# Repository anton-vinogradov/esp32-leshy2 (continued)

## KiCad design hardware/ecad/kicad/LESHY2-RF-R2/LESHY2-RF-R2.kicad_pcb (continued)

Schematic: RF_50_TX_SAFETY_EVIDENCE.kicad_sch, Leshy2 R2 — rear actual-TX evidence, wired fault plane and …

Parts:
C262, C287, C288: TDK C1608X7R1C105K080AC; C_0603_1608Metric
C263, C264, C265, C266, C267, C268, C269, C270, C271, C272, C273, C274, C276, C277, C278, C280, C282, C283, C284, C285, C286: Yageo CC0402KRX7R9BB104; C_0402_1005Metric
C275: Murata GRM21BR71E225KE11L; C_0805_2012Metric
C279: Murata GRM188R60J106ME47D; C_0603_1608Metric
C281: Murata GRM155R71H103KA88D; C_0402_1005Metric
J13: Samtec FTSH-105-01-L-DV-K-P-TR; FTSH-105-01-L-DV-K-P-TR
Q6: NX3008NBKS,115; SOT-363_SC-70-6
R249, R250, R252, R253, R255, R256, R257, R258, R259, R260, R261, R263, R266, R267, R268, R269, R271, R273, R274, R275, R276, R277, R278, R279, R280, R282, R283, R285, R287: Yageo RC0402FR-0710KL; R_0402_1005Metric
R251, R262, R281, R286: Yageo RC0402FR-071ML; R_0402_1005Metric
R254, R264, R270, R284, R288: Yageo RC0402FR-07100KL; R_0402_1005Metric
R265, R272: Yageo RC0402FR-0747KL; R_0402_1005Metric
SW5: C&K JS102011SAQN; SW_SPDT_CK_JS102011SAQN
U107, U133, U134: Diodes Incorporated BAT54-7-F; SOT-23
U108, U109, U110: TLV1821DCKR; Texas_R-PDSO-G5_DCK-5
U111: TCA9535PWR; TSSOP-24_4.4x7.8mm_P0.65mm
U112, U113, U114, U115, U116: BAT54ALT1G; SOT-23
U117: 74LVC2G14GV,125; SC-74-6_1.55x2.9mm_P0.95mm
U118: SN74LVC3G07DCUR; VSSOP-8_2.3x2mm_P0.5mm
U119: SN74LVC08APWR; TSSOP-14_4.4x5mm_P0.65mm
U120: SN74LVC1G74DCUR; VSSOP-8_2.3x2mm_P0.5mm
U121: 74LVC1G32GV,125; SC-74A-5_1.55x2.9mm_P0.95mm
U122: SN74LVC1G17DCKR; SOT-353_SC-70-5
U123: Texas Instruments SN74LVC1G06DCKR; Texas_R-PDSO-G5_DCK-5
U124, U128, U129, U131, U132: SN74LVC1G07DCKR; Texas_R-PDSO-G5_DCK-5
U125: TPS3808G33DBVR; SOT-23-6
U126: Texas Instruments TPD4E05U06DQAR; USON-10_2.5x1.0mm_P0.5mm
U127: Texas Instruments MSPM0C1106SDGS20R; Texas_DGS0020A_TSSOP-20_3x5.1mm_P0.5mm
U130: Texas Instruments TPS3435CAKAGDDFR; Texas_DDF0008A_SOT-8_1.6x2.9mm_P0.65mm

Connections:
/RF_01_USB_PD_CHARGE/AON_SAFE_3V3: C263.1 (END_1), C264.1 (END_1), C265.1 (END_1), C266.1 (END_1), C269.1 (END_1), C270.1 (END_1), C271.1 (END_1), C272.1 (END_1), C273.1 (END_1), C274.1 (END_1), C276.1 (END_1), C277.1 (END_1), C278.1 (END_1), C279.1 (END_1), C280.1 (END_1), C282.1 (END_1), C283.1 (END_1), C284.1 (END_1), C285.1 (END_1), C286.1 (END_1), J13.2, R249.1 (END_1), R252.1 (END_1), R254.1 (END_1), R259.1 (END_1), R260.1 (END_1), R261.1 (END_1), R263.1 (END_1), R267.1 (END_1), R268.1 (END_1), R269.1 (END_1), R272.1 (END_1), R275.1 (END_1), R277.1 (END_1), R282.1 (END_1), R284.1 (END_1), R288.1 (END_1), U108.5 (VPLUS), U109.5 (VPLUS), U110.5 (VPLUS), U111.24 (VCC), U117.5 (VCC), U118.8 (VCC), U119.14 (VCC), U120.7 (PRE_N), U120.8 (VCC), U121.5 (VCC), U122.5 (VCC), U123.5 (VCC), U124.5 (VCC), U125.5 (SENSE), U125.6 (VDD), U127.6 (VDD), U128.5 (VCC), U129.5 (VCC), U130.6 (WD_EN), U130.8 (VDD), U131.5 (VCC), U132.5 (VCC); also elsewhere on the board
/RF_01_USB_PD_CHARGE/POWER_GROUND: C262.2 (END_2), C263.2 (END_2), C264.2 (END_2), C265.2 (END_2), C266.2 (END_2), C267.2 (END_2), C268.2 (END_2), C269.2 (END_2), C270.2 (END_2), C271.2 (END_2), C272.2 (END_2), C273.2 (END_2), C274.2 (END_2), C275.2 (END_2), C276.2 (END_2), C277.2 (END_2), C278.2 (END_2), C279.2 (END_2), C280.2 (END_2), C281.2 (END_2), C282.2 (END_2), C283.2 (END_2), C284.2 (END_2), C285.2 (END_2), C286.2 (END_2), C287.2 (END_2), C288.2 (END_2), J13.1, J13.7, J13.9, Q6.1 (S1), Q6.2 (G1), Q6.4 (S2), R250.2 (END_2), R253.2 (END_2), R255.2 (END_2), R256.2 (END_2), R257.2 (END_2), R258.2 (END_2), R262.2 (END_2), R273.2 (END_2), R274.2 (END_2), R276.2 (END_2), R280.2 (END_2), R283.2 (END_2), R285.2 (END_2), R287.2 (END_2), SW5.2 (COMMON), U108.2 (VMINUS), U109.2 (VMINUS), U110.2 (VMINUS), U111.2 (A1), U111.3 (A2), U111.12 (GND), U111.21 (A0), U117.2 (GND), U118.4 (GND), U119.7 (GND), U120.4 (GND), U121.3 (GND), U122.3 (GND), U123.3 (GND), U124.3 (GND), U125.2 (GND), U126.3 (GND_3), U126.8 (GND_8), U127.7 (VSS), U128.3 (GND), U129.3 (GND), U130.1 (SET0), U130.4 (GND), U130.5 (SET1), U131.3 (GND), U132.3 (GND); also elsewhere on the board
/RF_02_PACK_SAFETY_AON/3V3_MAIN: R266.1 (END_1), R271.1 (END_1), R278.1 (END_1), R279.1 (END_1); also elsewhere on the board
/RF_02_PACK_SAFETY_AON/HUB_SAFE_I2C_SCL_AON: U127.11 (PA11); also elsewhere on the board
/RF_02_PACK_SAFETY_AON/HUB_SAFE_I2C_SDA_AON: U127.4 (PA0); also elsewhere on the board
/RF_02_PACK_SAFETY_AON/PACK_ADMISSION_VDD: R265.1 (END_1); also elsewhere on the board
/RF_03_MAIN_RAILS_DOMAIN_GATES/AON_PG_N: U125.3 (MR_N); also elsewhere on the board
/RF_03_MAIN_RAILS_DOMAIN_GATES/EV_N8_LORA_EXT: U111.13 (P10), U116.1 (K1); also elsewhere on the board
/RF_03_MAIN_RAILS_DOMAIN_GATES/EXT_ANY_5V_EN_SAFE: U119.11 (4Y); also elsewhere on the board
/RF_03_MAIN_RAILS_DOMAIN_GATES/EXT_ANY_5V_REQ: U119.12 (4A); also elsewhere on the board
/RF_03_MAIN_RAILS_DOMAIN_GATES/FAULT_ASSERT_N: R262.1 (END_1), R263.2 (END_2), R264.1 (END_1), R277.2 (END_2), U118.1 (1A), U118.2 (3Y), U118.3 (2A), U119.10 (3B), U124.4 (Y), U128.4 (Y), U130.7 (WDO_N); also elsewhere on the board
/RF_03_MAIN_RAILS_DOMAIN_GATES/POR_N: R269.2 (END_2), U119.9 (3A), U125.1 (RESET_N); also elsewhere on the board
/RF_03_MAIN_RAILS_DOMAIN_GATES/POWER_FAULT_N: R266.2 (END_2), U127.3 (PA30); also elsewhere on the board
/RF_03_MAIN_RAILS_DOMAIN_GATES/POWER_ZONE_TEMP_ADC: U127.1 (PA26); also elsewhere on the board
/RF_03_MAIN_RAILS_DOMAIN_GATES/RF_ZONE_TEMP_ADC: U127.2 (PA27); also elsewhere on the board
/RF_10_RP2354_CORE_SERVICE/CC_PWR_EN: U119.1 (1A); also elsewhere on the board
/RF_10_RP2354_CORE_SERVICE/RF_ANY_TX_N: U132.4 (Y); also elsewhere on the board
/RF_10_RP2354_CORE_SERVICE/RF_RP_RESET_N: Q6.3 (D2), U118.7 (1Y); also elsewhere on the board
/RF_10_RP2354_CORE_SERVICE/RF_SLOW_IO_ALERT: U117.4 (2Y); also elsewhere on the board
/RF_10_RP2354_CORE_SERVICE/VOICE_PTT_REQ_N: U121.2 (1A); also elsewhere on the board
/RF_20_CC1101_VOICE_TX/CC_DETECT_V: U108.4 (IN_N); also elsewhere on the board
/RF_20_CC1101_VOICE_TX/CC_PWR_EN_PRIMARY: U119.3 (1Y); also elsewhere on the board
/RF_20_CC1101_VOICE_TX/CC_PWR_EN_SAFE: U107.1 (A); also elsewhere on the board
/RF_20_CC1101_VOICE_TX/VOICE_DETECT_V: U109.4 (IN_N); also elsewhere on the board
/RF_20_CC1101_VOICE_TX/VOICE_DOMAIN_EN_SAFE: U119.6 (2Y), U133.1 (A), U134.1 (A); also elsewhere on the board
/RF_20_CC1101_VOICE_TX/VOICE_EFUSE_BACKUP_EN_N: U118.5 (2Y); also elsewhere on the board
/RF_20_CC1101_VOICE_TX/VOICE_PTT_SAFE_N: U121.4 (1Y); also elsewhere on the board
/RF_20_CC1101_VOICE_TX/VOICE_V_DETECT_V: U110.4 (IN_N); also elsewhere on the board
/RF_30_U214_U219_M5_EXT/EV_N9_U219_NFC: U111.20 (P17), U116.2 (K2); also elsewhere on the board
/RF_31_REAR_CONTROLS/VOICE_DOMAIN_REQ: U119.4 (2A); also elsewhere on the board
/RF_40_INTERBOARD_M1/S3_RESET_KILL_GATE: U129.4 (Y); also elsewhere on the board
/RF_40_INTERBOARD_M1/UI_ZONE_TEMP_ADC: U127.12 (PA16); also elsewhere on the board
/RF_50_TX_SAFETY_EVIDENCE/ANY_TX_AON_N: R249.2 (END_2), U112.3 (A_COMMON), U113.3 (A_COMMON), U114.3 (A_COMMON), U115.3 (A_COMMON), U116.3 (A_COMMON), U127.17 (PA22), U132.2 (A)
/RF_50_TX_SAFETY_EVIDENCE/AON_SERVICE_RELEASE_REQ: R257.1 (END_1), U111.17 (P14); also elsewhere on the board
/RF_50_TX_SAFETY_EVIDENCE/C5_MUX_SEL_REQUEST: R255.1 (END_1), U111.15 (P12); also elsewhere on the board
/RF_50_TX_SAFETY_EVIDENCE/C5_SERVICE_OWNED: R258.1 (END_1), U111.18 (P15); also elsewhere on the board
/RF_50_TX_SAFETY_EVIDENCE/C5_SERVICE_PATH_ACK: R256.1 (END_1), U111.16 (P13); also elsewhere on the board
/RF_50_TX_SAFETY_EVIDENCE/CC_EVIDENCE_HOLD: C262.1 (END_1), R250.1 (END_1), U107.3 (K); also elsewhere on the board
/RF_50_TX_SAFETY_EVIDENCE/EV_N0_S3: U111.4 (P00), U112.1 (K1); also elsewhere on the board
/RF_50_TX_SAFETY_EVIDENCE/EV_N1_C5: U111.5 (P01), U112.2 (K2); also elsewhere on the board
/RF_50_TX_SAFETY_EVIDENCE/EV_N2_NRF0: U111.6 (P02), U113.1 (K1); also elsewhere on the board
/RF_50_TX_SAFETY_EVIDENCE/EV_N3_NRF1: U111.7 (P03), U113.2 (K2); also elsewhere on the board
/RF_50_TX_SAFETY_EVIDENCE/EV_N4_NRF2: U111.8 (P04), U114.1 (K1); also elsewhere on the board
/RF_50_TX_SAFETY_EVIDENCE/EV_N5_CC: R251.1 (END_1), R252.2 (END_2), U108.1 (OUT), U111.9 (P05), U114.2 (K2); also elsewhere on the board
/RF_50_TX_SAFETY_EVIDENCE/EV_N6_VOICE: R281.1 (END_1), R282.2 (END_2), R286.1 (END_1), U109.1 (OUT), U110.1 (OUT), U111.10 (P06), U115.1 (K1); also elsewhere on the board
/RF_50_TX_SAFETY_EVIDENCE/EV_N7_IR: U111.11 (P07), U115.2 (K2); also elsewhere on the board
/RF_50_TX_SAFETY_EVIDENCE/EV_THRESH_5_CC: R251.2 (END_2), R253.1 (END_1), R254.2 (END_2), U108.3 (IN_P)
/RF_50_TX_SAFETY_EVIDENCE/EV_THRESH_6_VOICE: R281.2 (END_2), R283.1 (END_1), R284.2 (END_2), U109.3 (IN_P)
/RF_50_TX_SAFETY_EVIDENCE/EV_THRESH_6_VOICE_V: R286.2 (END_2), R287.1 (END_1), R288.2 (END_2), U110.3 (IN_P)
/RF_50_TX_SAFETY_EVIDENCE/FAULT_ASSERT_SENSE: R264.2 (END_2), U111.14 (P11)
/RF_50_TX_SAFETY_EVIDENCE/FAULT_KILL: U120.3 (Q_N), U121.1 (1B), U131.2 (A); also elsewhere on the board
/RF_50_TX_SAFETY_EVIDENCE/FAULT_LATCH_SENSE: R278.2 (END_2), U131.4 (Y); also elsewhere on the board
/RF_50_TX_SAFETY_EVIDENCE/HUB_AON_ALERT_N: R259.2 (END_2), U111.19 (P16); also elsewhere on the board
/RF_50_TX_SAFETY_EVIDENCE/POWER_COMMAND_OFF_N: C267.1 (END_1), R265.2 (END_2), SW5.3 (THROW_B), U118.6 (3A); also elsewhere on the board
/RF_50_TX_SAFETY_EVIDENCE/RF_RESET_KILL_GATE: Q6.5 (G2), R271.2 (END_2), U123.4 (Y)
/RF_50_TX_SAFETY_EVIDENCE/RF_SLOW_IO_INT_N: R279.2 (END_2), U117.3 (2A); also elsewhere on the board
/RF_50_TX_SAFETY_EVIDENCE/RUN_EDGE: R270.1 (END_1), U117.6 (1Y), U124.2 (A), U127.19 (PA24)
/RF_50_TX_SAFETY_EVIDENCE/RUN_LOOP_RAW: C268.1 (END_1), R267.2 (END_2), SW5.1 (THROW_A), U117.1 (1A), U126.1 (D1_PLUS)
/RF_50_TX_SAFETY_EVIDENCE/RUN_PERMIT: U119.2 (1B), U119.5 (2B), U119.13 (4B), U120.5 (Q), U123.2 (A); also elsewhere on the board
/RF_50_TX_SAFETY_EVIDENCE/S3_FAULT_RESET_REQUEST: R274.1 (END_1), U127.18 (PA23), U129.2 (A)
/RF_50_TX_SAFETY_EVIDENCE/SAFETY_CONTROLLER_NRST_N: C281.1 (END_1), J13.3, R272.2 (END_2), U127.5 (PA1_NRST)
/RF_50_TX_SAFETY_EVIDENCE/SAFETY_EVIDENCE_I2C_SCL: R260.2 (END_2), U111.22 (SCL), U127.8 (PA2)
/RF_50_TX_SAFETY_EVIDENCE/SAFETY_EVIDENCE_I2C_SDA: R261.2 (END_2), U111.23 (SDA), U127.9 (PA4)
/RF_50_TX_SAFETY_EVIDENCE/SAFETY_FAULT_REQUEST: R273.1 (END_1), U127.20 (PA25), U128.2 (A)
/RF_50_TX_SAFETY_EVIDENCE/SAFETY_SERVICE_UART_RX: J13.5, U127.14 (PA18)
/RF_50_TX_SAFETY_EVIDENCE/SAFETY_SERVICE_UART_TX: J13.4, U127.13 (PA17)
/RF_50_TX_SAFETY_EVIDENCE/SAFETY_SWCLK: J13.8, U127.16 (PA20_SWCLK)
/RF_50_TX_SAFETY_EVIDENCE/SAFETY_SWDIO: J13.6, U127.15 (PA19_SWDIO)
/RF_50_TX_SAFETY_EVIDENCE/SAFETY_WATCHDOG_MR_N: R275.2 (END_2), U130.2 (MR_N)
/RF_50_TX_SAFETY_EVIDENCE/SAFETY_WATCHDOG_WDI: R276.1 (END_1), U127.10 (PA6), U130.3 (WDI)
/RF_50_TX_SAFETY_EVIDENCE/SAFE_CLEAR_N: U119.8 (3Y), U120.6 (CLR_N)
/RF_50_TX_SAFETY_EVIDENCE/SAFE_D_HIGH: R268.2 (END_2), U120.2 (D)
/RF_50_TX_SAFETY_EVIDENCE/SAFE_REARM_CLK: U120.1 (CLK), U122.4 (Y)
/RF_50_TX_SAFETY_EVIDENCE/SAFE_REARM_DELAY: C275.1 (END_1), R270.2 (END_2), U122.2 (A)
/RF_50_TX_SAFETY_EVIDENCE/VOICE_EVIDENCE_HOLD: C287.1 (END_1), R280.1 (END_1), U133.3 (K); also elsewhere on the board
/RF_50_TX_SAFETY_EVIDENCE/VOICE_V_EVIDENCE_HOLD: C288.1 (END_1), R285.1 (END_1), U134.3 (K); also elsewhere on the board

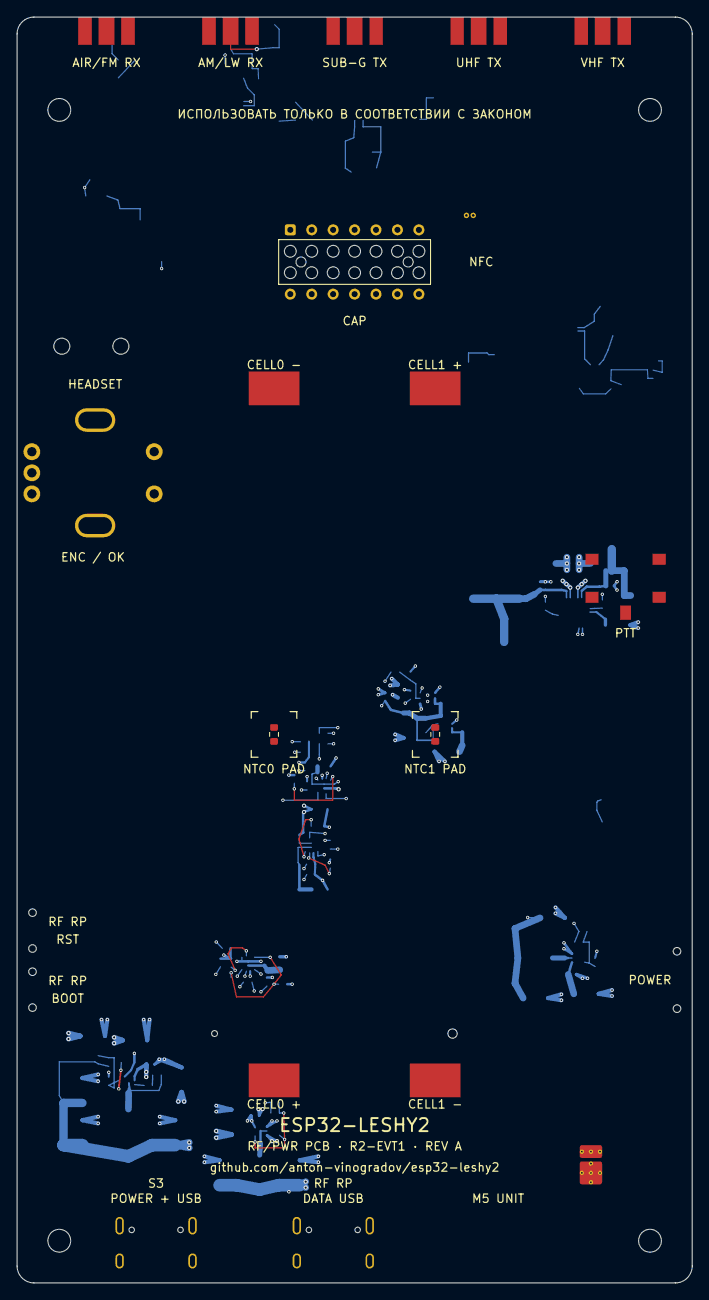
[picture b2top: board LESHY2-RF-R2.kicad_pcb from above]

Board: 6 copper layers, 80.0 x 150.0 mm, 784 parts (768 on the bottom side), 516 nets.

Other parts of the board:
MH1, MH2, MH3, MH4: M2.5 compression-stop axis; MountingHole_2.7mm_M2.5

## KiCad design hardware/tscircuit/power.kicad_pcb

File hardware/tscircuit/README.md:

# Current ECAD status

There is **no current Leshy2 schematic or PCB layout in this directory yet**.
The previous tscircuit sheets and their partial KiCad exports were moved to
[`drafts/legacy-2026-08-22/tscircuit-pre-g2f3i`](../../drafts/legacy-2026-08-22/tscircuit-pre-g2f3i/)
because they describe a superseded device: 80-mm boards, a 4-inch ST7796
display, discrete D-pad buttons, STOP, onboard LoRa, SA868 and the old
controller/resource assignment.

Those files are retained only as historical implementation material. They must
not be built, reviewed as the current circuit or sent to a PCB manufacturer.

The current electrical source is the machine-reviewed `G2F-3I` architecture in
[`hardware/architecture`](../architecture/). H1 has been accepted and H2 now
authorizes a new reviewable production schematic generated from that source.
KiCad PCB placement and routing remain unauthorized until the current
schematic, ERC, power/fault simulation and joined mechanical/electrical/firmware
review pass.

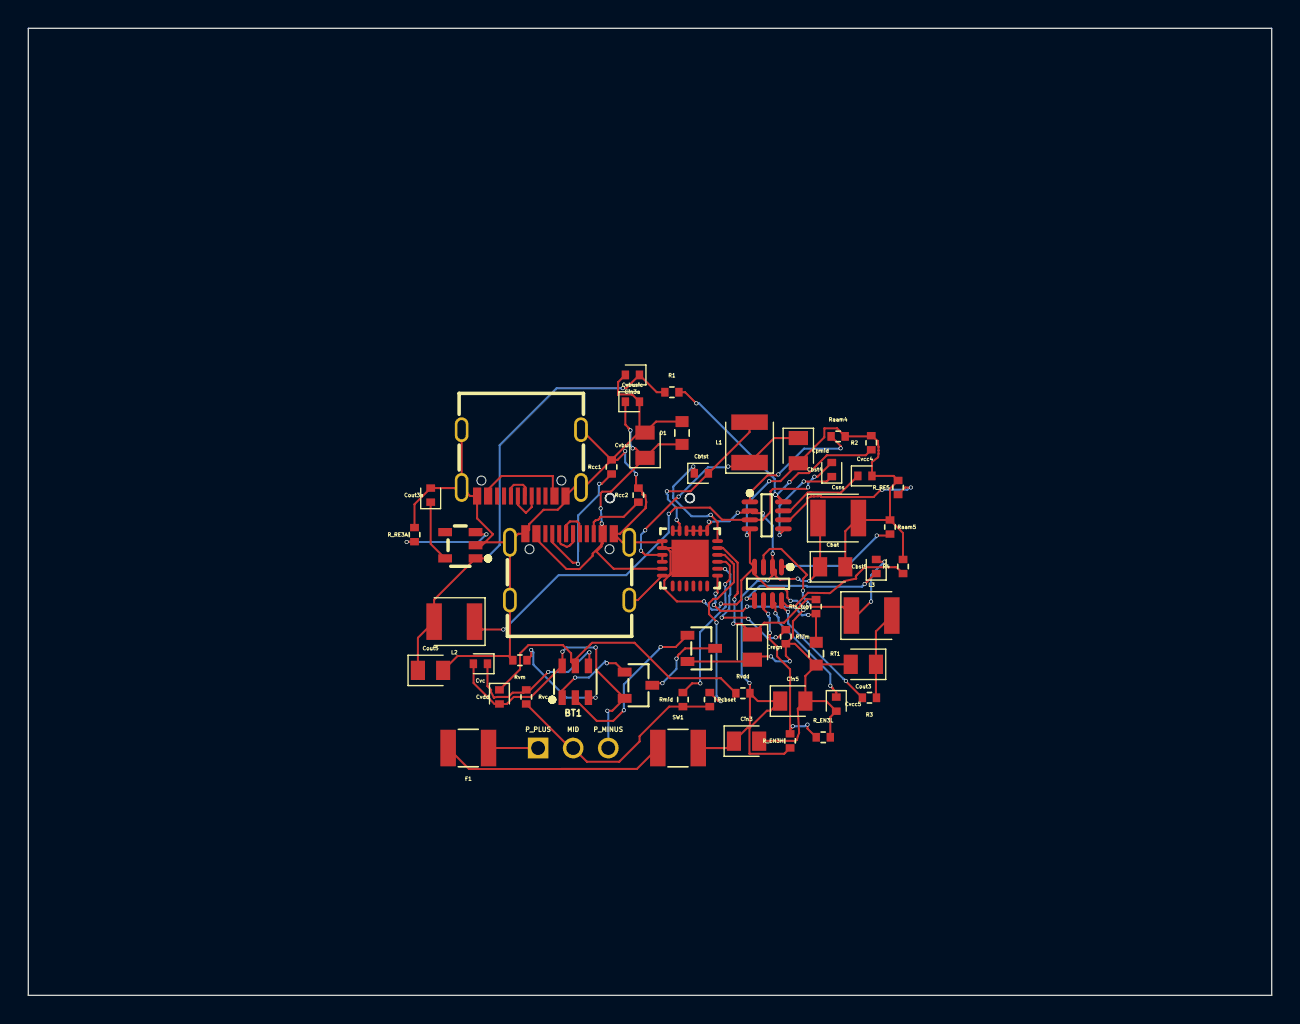
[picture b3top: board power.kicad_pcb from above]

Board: 2 copper layers, 90.0 x 70.0 mm, 55 parts (0 on the bottom side), 44 nets.

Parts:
BT1: chip_pinrow3
Cbat: 10uF; capacitor_cap0805
Cbst4, Cbst5: 100nF; capacitor_cap0402
Cbtst: 47nF; capacitor_cap0402
Cin3, Cin5: 22uF; capacitor_cap0805
Cin3a: 1uF; capacitor_cap0402
Cout3, Cout5: 22uF; capacitor_cap0805
Cout3a: 2.2uF; capacitor_cap0402
Cpmid: 10uF; capacitor_cap0805
Cregn: 4.7uF; capacitor_cap0805
Csns: 47uF; capacitor_cap1210
Cvbus: 10uF; capacitor_cap0805
Cvbusic: 1uF; capacitor_cap0402
Cvc: 0.1uF; capacitor_cap0402
Cvcc4, Cvcc5: 0.1uF; capacitor_cap0402
Cvdd: 0.1uF; capacitor_cap0402
D1: 1MΩ; resistor_res0603
F1: 50mΩ; resistor_res1210
J1, J2: chip
L1, L3: 2.2µH; inductor_1210
L2: 4.7µH; inductor_1210
Q1, Q2: chip
R1: 52.3kΩ; resistor_res0402
R2, R4: 10kΩ; resistor_res0402
R3: 31.6kΩ; resistor_res0402
RT1: 10kΩ; resistor_res0603
R_EN3H: 100kΩ; resistor_res0402
R_EN3L: 47kΩ; resistor_res0402
R_RE3A, R_RE5: 100kΩ; resistor_res0402
Raam4, Raam5: 100kΩ; resistor_res0402
Rcbset: 10Ω; resistor_res0402
Rcc1, Rcc2: 5.1kΩ; resistor_res0402
Rilim: 383Ω; resistor_res0402
Rmid: 300Ω; resistor_res0402
Rts_top: 5.23kΩ; resistor_res0402
Rvc: 470Ω; resistor_res0402
Rvdd: 470Ω; resistor_res0402
Rvm: 2kΩ; resistor_res0402
SW1: 10mΩ; resistor_res1210
U2, U3, U4, U5, U6: chip

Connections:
.BT1 > .P_PLUS to .F1 > .pin1: BT1.1, F1.1
.Cbst4 > .pin1 to .U4 > .BST: Cbst4.1, U4.5
.Cbst5 > .pin1 to .U5 > .BST: Cbst5.1, U5.5
.Cbtst > .pin1 to .U2 > .BTST: Cbtst.1, U2.12
.Cregn > .pin1 to .U2 > .REGN: Cregn.1, Rts_top.1, U2.11
.Cvcc4 > .pin1 to .U4 > .VCC: Cvcc4.1, U4.7
.Cvcc5 > .pin1 to .U5 > .VCC: Cvcc5.1, U5.7
.F1 > .pin2 to .SW1 > .pin1: F1.2, SW1.1
.R1 > .pin2 to .U4 > .FB: R1.2, R2.1, U4.8
.R3 > .pin2 to .U5 > .FB: R3.2, R4.1, U5.8
.R_EN3H > .pin2 to .U5 > .pin6: R_EN3H.2, R_EN3L.1, U5.6
.Raam4 > .pin1 to .U4 > .AAM: Raam4.1, U4.1
.Raam5 > .pin1 to .U5 > .AAM: Raam5.1, U5.1
.Rcbset > .pin1 to .U2 > .CBSET: Rcbset.1, U2.10
.Rcc1 > .pin1 to .J1 > .CC1: J1.13, Rcc1.1
.Rcc2 > .pin1 to .J1 > .CC2: J1.7, Rcc2.1
.Rilim > .pin1 to .U2 > .ILIM: Rilim.1, U2.8
.Rmid > .pin1 to .U2 > .MID: Rmid.1, U2.9
.Rvc > .pin1 to .U3 > .VC: Cvc.1, Rvc.1, U3.4
.Rvdd > .pin1 to .U3 > .VDD: Cvdd.1, Rvdd.1, U3.5
.Rvm > .pin1 to .U3 > .VM: Rvm.1, U3.3
.U3 > .CO to .Q2 > .G: Q2.1, U3.2
.U3 > .DO to .Q1 > .G: Q1.1, U3.1
.U4 > .SW to .L2 > .pin1: Cbst4.2, L2.1, U4.3
.U5 > .SW to .L3 > .pin1: Cbst5.2, L3.1, U5.3
BAT: Cbat.1, Cin3.1, Cin5.1, Csns.1, R_EN3H.1, Rvdd.2, SW1.2, U2.13, U2.14, U2.15, U2.16, U4.2, U5.2
BATM: BT1.2, Rcbset.2, Rmid.2, Rvc.2
BMINUS: BT1.3, Cvc.2, Cvdd.2, Q1.2, U3.6
GND: Cbat.2, Cin3.2, Cin3a.2, Cin5.2, Cout3.2, Cout3a.2, Cout5.2, Cpmid.2, Cregn.2, Csns.2, Cvbus.2, Cvbusic.2, Cvcc4.2, Cvcc5.2, D1.2, J1.1, J1.2, J1.3, J1.4, J1.5, J1.16, J2.1, J2.2, J2.3, J2.4, J2.5, J2.16, Q2.2, R2.2, R4.2, RT1.2, R_EN3L.2, R_RE3A.2, R_RE5.2, Raam4.2, Raam5.2, Rcc1.2, Rcc2.2, Rilim.2, Rvm.2, U2.19, U2.20, U2.24, U2.25, U4.4, U5.4, U6.2
PACKMID: Q1.3, Q2.3
PMID: Cpmid.1, L1.1, U2.21, U2.22
RAIL_EN_3V3A: R_RE3A.1, U6.3
RAIL_EN_5V: R_RE5.1, U4.6
SW: Cbtst.2, L1.2, U2.17, U2.18
TS: RT1.1, Rts_top.2, U2.7
USB_DM_C5: J2.10, J2.12
USB_DM_S3: J1.10, J1.12
USB_DP_C5: J2.9, J2.11
USB_DP_S3: J1.9, J1.11
V3V3: Cout3.1, L3.2, R3.1
V3V3A: Cout3a.1, U6.5
V5: Cin3a.1, Cout5.1, L2.2, R1.1, U6.1
VBUS_C5: J2.6, J2.15
VBUS_S3: Cvbus.1, Cvbusic.1, D1.1, J1.6, J1.15, U2.23

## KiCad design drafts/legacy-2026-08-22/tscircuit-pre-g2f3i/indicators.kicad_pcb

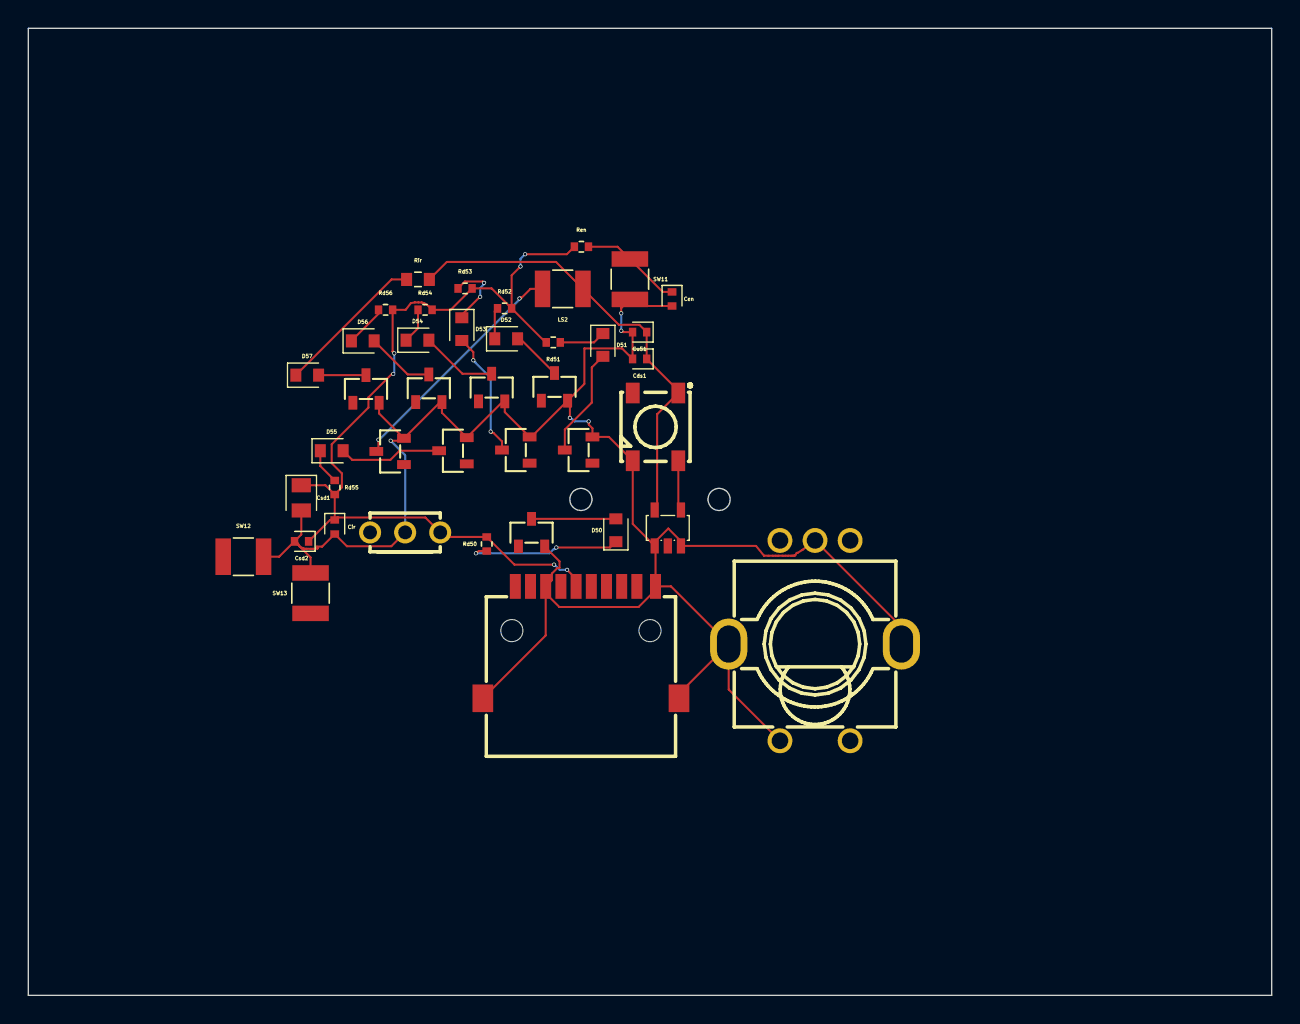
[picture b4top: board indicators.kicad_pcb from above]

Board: 2 copper layers, 90.0 x 70.0 mm, 41 parts (0 on the bottom side), 22 nets.

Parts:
Cds1: 100nF; capacitor_cap0402
Cen: 1uF; capacitor_cap0402
Cir: 100nF; capacitor_cap0402
Csd1: 10uF; capacitor_cap0805
Csd2: 100nF; capacitor_cap0402
Cu51: 100nF; capacitor_cap0402
D50, D51, D52, D53, D54, D55, D56, D57: LED; led_0603
DS1: chip
J50: chip
LS2: 10mΩ; resistor_res1210
Q50, Q51, Q52, Q53, Q54, Q55, Q56, Q57, Q58: chip
Rd50, Rd51, Rd52, Rd53, Rd54, Rd55, Rd56: 4.7kΩ; resistor_res0402
Ren: 10kΩ; resistor_res0402
Rir: 47Ω; resistor_res0603
SW10: chip
SW11, SW12, SW13: 10mΩ; resistor_res1210
U50, U51: chip

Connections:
.D50 > .pin1 to .Rd50 > .pin1: D50.1, Rd50.1
.D50 > .pin2 to .Q50 > .C: D50.2, Q50.3
.D51 > .pin1 to .Rd51 > .pin1: D51.1, Rd51.1
.D51 > .pin2 to .Q51 > .C: D51.2, Q51.3
.D52 > .pin1 to .Rd52 > .pin1: D52.1, Rd52.1
.D52 > .pin2 to .Q52 > .C: D52.2, Q52.3
.D53 > .pin1 to .Rd53 > .pin1: D53.1, Rd53.1
.D53 > .pin2 to .Q53 > .C: D53.2, Q53.3
.D54 > .pin1 to .Rd54 > .pin1: D54.1, Rd54.1
.D54 > .pin2 to .Q54 > .C: D54.2, Q54.3
.D55 > .pin1 to .Rd55 > .pin1: D55.1, Rd55.1
.D55 > .pin2 to .Q55 > .C: D55.2, Q55.3
.D56 > .pin1 to .Rd56 > .pin1: D56.1, Rd56.1
.D56 > .pin2 to .Q56 > .C: D56.2, Q56.3
.D57 > .pin1 to .Rir > .pin1: D57.1, Rir.1
.D57 > .pin2 to .Q58 > .C: D57.2, Q58.3
.LS2 > .pin2 to .Q57 > .C: LS2.2, Q57.3
.U51 > .Y to .DS1 > .DIN: DS1.4, U51.4
GND: Cds1.2, Cen.2, Cir.2, Csd1.2, Csd2.2, Cu51.2, DS1.3, J50.6, J50.10, J50.11, J50.12, Q50.2, Q51.2, Q52.2, Q53.2, Q54.2, Q55.2, Q56.2, Q57.2, Q58.2, SW10.2, SW10.4, SW10.6, SW10.7, SW11.2, SW12.2, SW13.2, U50.2, U51.1, U51.3
S3_EN: Cen.1, Ren.2, SW11.1
V3V3: Cir.1, Csd1.1, Csd2.1, J50.4, Rd50.2, Rd51.2, Rd52.2, Rd53.2, Rd54.2, Rd55.2, Rd56.2, Ren.1, U50.3
V5: Cds1.1, Cu51.1, DS1.1, LS2.1, Rir.2, U51.5

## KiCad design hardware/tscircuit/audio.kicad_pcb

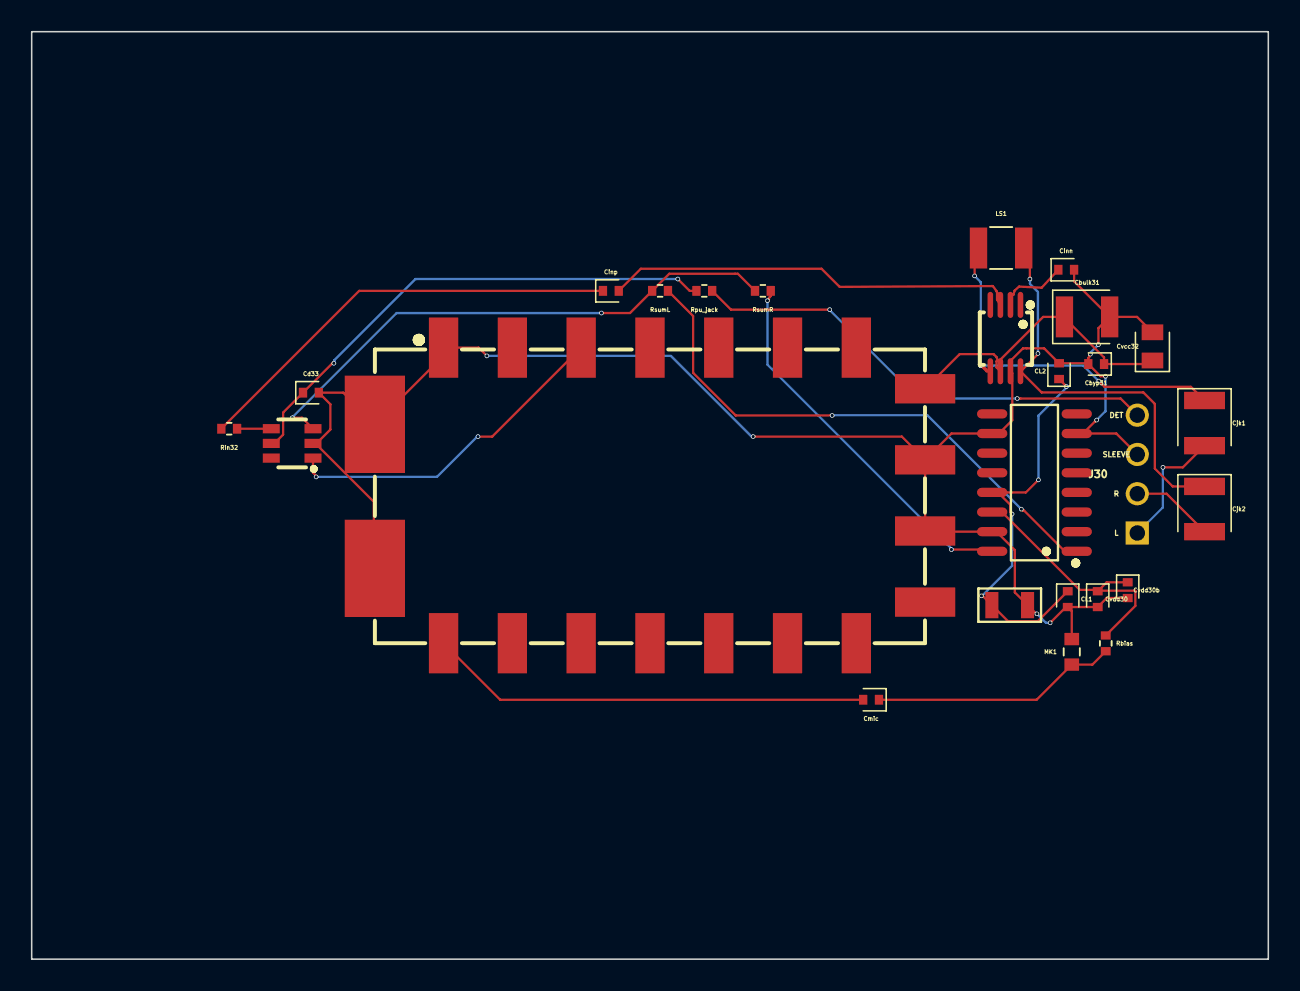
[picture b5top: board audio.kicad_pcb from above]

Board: 2 copper layers, 80.0 x 60.0 mm, 26 parts (0 on the bottom side), 20 nets.

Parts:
CL1, CL2: 12pF; capacitor_cap0402
Cbulk31: 330uF; capacitor_cap1210
Cbyp31: 100nF; capacitor_cap0402
Cd33: 100nF; capacitor_cap0402
Cinn: 0.1uF; capacitor_cap0402
Cinp: 0.1uF; capacitor_cap0402
Cjk1, Cjk2: 220uF; capacitor_cap1210
Cmic: 1uF; capacitor_cap0402
Cvcc32: 10uF; capacitor_cap0805
Cvdd30: 1uF; capacitor_cap0402
Cvdd30b: 100nF; capacitor_cap0402
J30: chip_pinrow4
LS1: 4Ω; resistor_res1210
MK1: 2.2kΩ; resistor_res0603
Rbias: 4.7kΩ; resistor_res0402
Rin32: 10kΩ; resistor_res0402
Rpu_jack: 10kΩ; resistor_res0402
RsumL: 10kΩ; resistor_res0402
RsumR: 10kΩ; resistor_res0402
U30, U31, U32, U33: chip
Y1: chip

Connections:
.Cinp > .pin2 to .U32 > .IN_POS: Cinp.2, U32.3
.Cjk1 > .pin2 to .J30 > .L: Cjk1.2, J30.1
.Cjk2 > .pin2 to .J30 > .R: Cjk2.2, J30.2
.Cmic > .pin2 to .U31 > .MIC_IN: Cmic.2, U31.18
.Rin32 > .pin2 to .Cinp > .pin1: Cinp.1, Rin32.2
.U30 > .RCLK to .Y1 > .OSC1: CL1.1, CL2.1, U30.13, Y1.1
.U30 > .pin1 to .RsumL > .pin1: RsumL.1, U30.1
.U30 > .pin16 to .RsumR > .pin1: RsumR.1, U30.16
.U32 > .IN_NEG to .Cinn > .pin1: Cinn.1, U32.2
GND: CL1.2, CL2.2, Cbulk31.2, Cbyp31.2, Cd33.2, Cinn.2, Cvcc32.2, Cvdd30.2, Cvdd30b.2, J30.3, MK1.2, U30.7, U30.10, U30.15, U31.1, U31.9, U31.10, U31.19, U31.20, U32.7, U33.2, Y1.2
JACK_DET: J30.4, Rpu_jack.1
MIC_HOT: Cmic.1, MK1.1, Rbias.2
MUX_OUT: Rin32.1, U33.4
SA_AF: U31.3, U33.1
SI_AUDIO: RsumL.2, RsumR.2, U33.3
SPK_M: Cjk2.1, LS1.2, U32.8
SPK_P: Cjk1.1, LS1.1, U32.5
V3V3: Cd33.1, Rpu_jack.2, U33.5
V3V3A: Cvdd30.1, Cvdd30b.1, Rbias.1, U30.14
V5: Cbulk31.1, Cbyp31.1, Cvcc32.1, U31.8, U32.6
